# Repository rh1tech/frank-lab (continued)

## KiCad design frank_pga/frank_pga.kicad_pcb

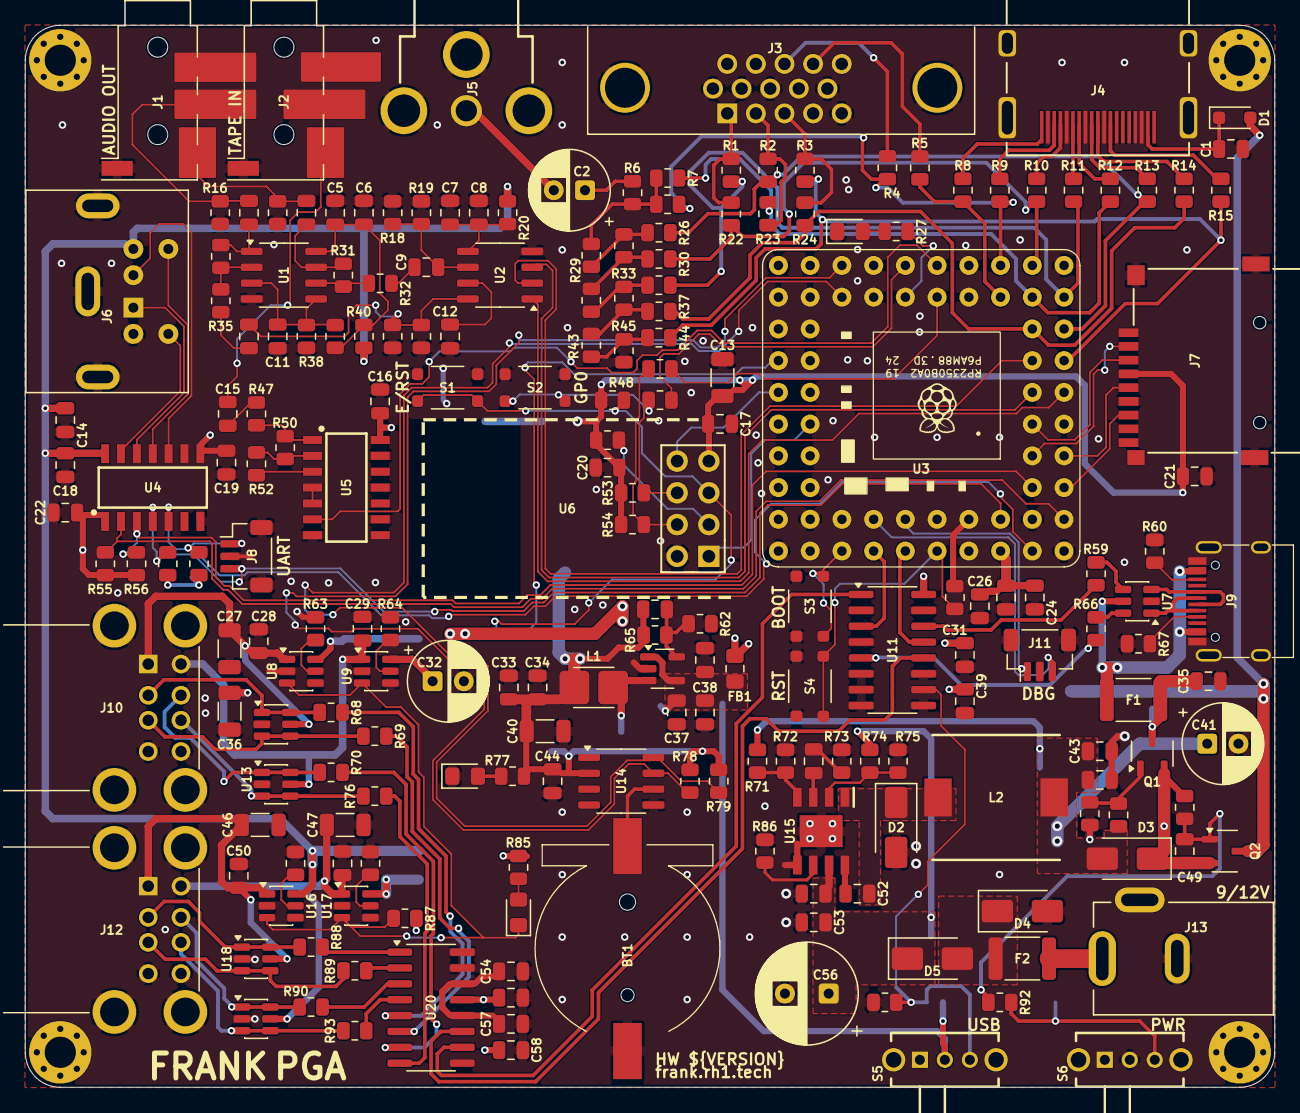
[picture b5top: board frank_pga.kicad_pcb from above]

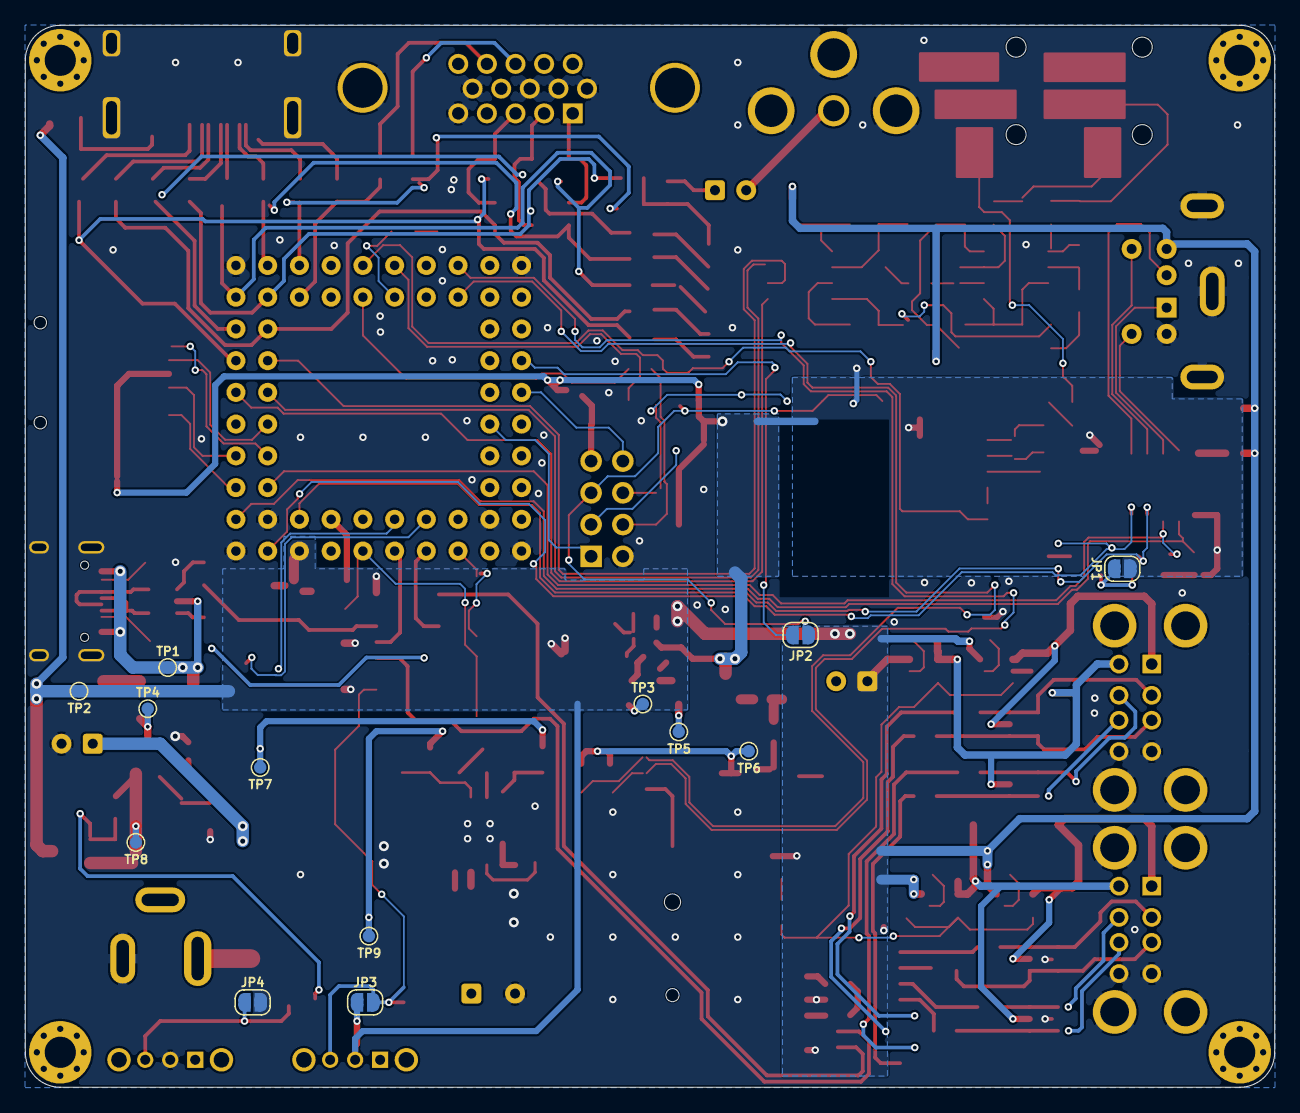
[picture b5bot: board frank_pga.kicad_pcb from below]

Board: 2 copper layers, 100.0 x 85.0 mm, 223 parts (13 on the bottom side), 150 nets.

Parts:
BT1: Battery_CR1220
C1, C5, C7, C14, C15, C16, C17, C18, C19, C21, C22, C24, C26, C28, C29, C37, C39, C44, C48, C50, C51, C52, C54, C55: 100n 50V; C_0805_2012Metric
C2, C32, C41: 220u 10V; C_Radial_D6.3mm_P2.50mm
C3, C4, C6, C8, C9, C10, C11, C12, C20, C23, C30, C31, C33, C34, C35, C38, C43, C45: 10u 16V; C_0805_2012Metric
C13, C27, C36, C40, C46, C47: 100u 10V; C_1206_3216Metric
C25: 22p 50V; C_0805_2012Metric
C42: 150p 50V; C_0805_2012Metric
C49, C57: 1u 16V; C_0805_2012Metric
C53: 10u 25V; C_0805_2012Metric
C56: 680u 25V; C_Radial_D8.0mm_P3.50mm
C58: 4.7u 16V; C_0805_2012Metric
D1: 1N5819WS; D_SOD-323
D2, D3, D5: SS34; D_SMA
D4: SMAJ15A; D_SMA
F1, F2: 1.5A 24V; Fuse_1812_4532Metric
FB1: 600R@100MHz 2A; L_0805_2012Metric
H1, H2, H3, H4: Hole 2.5mm; MountingHole_2.5mm_Pad_Via
J1: PJ-320D; AudioJack_3.5mm_PJ320D_AudioOut
J2: PJ-320D; AudioJack_3.5mm_PJ320D_TapeIn
J3: VGA; DSUB-15_Female
J4: HDMI-001 19PCBTP; HDMI_Female
J5: RCA-103; BarrelJack_RCJ-012
J6: MDC-036; MiniDIN_6pin_Female
J7: 104031-0811; MicroSD_SMD_Long
J8: UART M; JST_SH_1x03_P1.00mm_Vertical
J9: USB4215-03-A; USB_C_Receptacle
J10, J12: SS-52100-004; USB_A_Stacked
J11: DEBUG; JST_SH_1x03_P1.00mm_Vertical
J13: DC 9-12V; BarrelJack_DC-005
JP1: Mouse PU; SolderJumper-2_P1.3mm_Open_RoundedPad1.0x1.5mm
JP2: ESP RST; SolderJumper-2_P1.3mm_Open_RoundedPad1.0x1.5mm
JP3: USB Debug; SolderJumper-2_P1.3mm_Open_RoundedPad1.0x1.5mm
JP4: Force On; SolderJumper-2_P1.3mm_Open_RoundedPad1.0x1.5mm
L1: 2.2u; L_Cenker_CKCS3015_HandSolder
L2: 22u; Inductor_CDRH104RNP
LD1: Blue; LED_0805
LD2: Green; LED_0805
LD3: Red; LED_0805
Q1, Q2: AO3401A; SOT-23-3L_AOS
R1, R2, R3, R46, R49, R77, R81, R85: 1K; R_0805_2012Metric
R4, R5, R20, R27, R40: 100R; R_0805_2012Metric
R6: 51R; R_0805_2012Metric
R7, R8, R9, R10, R11, R12, R13, R14, R15, R26, R30, R34, R37, R44: 270R; R_0805_2012Metric
R16, R17: 20K; R_0805_2012Metric
R18, R42: 470R; R_0805_2012Metric
R19, R32, R35, R38, R39, R41, R48, R51, R53, R54, R55, R56, R57, R58, R61, R91, R92: 10K; R_0805_2012Metric
R21: 750R; R_0805_2012Metric
R22, R23, R24: 330R; R_0805_2012Metric
R25, R29, R33, R36, R43: 150R; R_0805_2012Metric
R28, R31, R71: 47K; R_0805_2012Metric
R45: 300R; R_0805_2012Metric
R47, R78, R79: 4.7K; R_0805_2012Metric
R50, R52, R63, R64, R65, R73, R74, R80, R82, R83, R84, R86, R87: 100K; R_0805_2012Metric
R59, R66, R68, R69, R70, R76, R88, R89, R90, R93: 22R; R_0805_2012Metric
R60, R67: 5.1K; R_0805_2012Metric
R62: 22K; R_0805_2012Metric
R72: 8.2K; R_0805_2012Metric
R75: 30K; R_0805_2012Metric
S1: ESP Reset; Button_SMD_3x4x2mm
S2: ESP Boot; Button_SMD_3x4x2mm
S3: RP Boot; Button_SMD_3x4x2mm
S4: RP Reset; Button_SMD_3x4x2mm
S5: USB MODE; Switch_Slide_SK12D07VG3NS
S6: POWER; Switch_Slide_SK12D07VG3NS
TP1: VBUS_USB; TestPoint_Pad_D1.0mm
TP2: VBUS; TestPoint_Pad_D1.0mm
TP3: +5V_BUCK; TestPoint_Pad_D1.0mm
TP4: VBUS_USB_F; TestPoint_Pad_D1.0mm
TP5: LX; TestPoint_Pad_D1.0mm
TP6: +3V3; TestPoint_Pad_D1.0mm
TP7: +5V_DC; TestPoint_Pad_D1.0mm
TP8: +5V_SEL; TestPoint_Pad_D1.0mm
TP9: VIN_PROT; TestPoint_Pad_D1.0mm
U1: LM358; SO-8
U2: TDA1387T; SO-8
U3: Pimoroni PGA2350; PGA2350
U4: TXS0104EDR; SOIC-14_P1.27mm
U5: CD4069UBM; SOIC-14_P1.27mm
U6: ESP-01 socket; ESP-01S
U7, U12, U13, U18, U19: USBLC6-2SC6; SOT-23-6
U8, U9, U16, U17: CH217K; SOT-23-6
U10: SY8089AAAC; SOT-23-5
U11: 74HC4052D; SOP-16_P1.27mm
U14: DS3231MZ; SO-8
U15: MP1584EN; SOIC-9_P1.27mm
U20: MW7211A; SOP-16_P1.27mm

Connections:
+3V3: C13.1, C16.1, C17.1, C19.1, C20.1, C21.2, C22.1, C25.1, C33.1, C34.1, C40.1, C44.1, J7.4 (VDD), JP1.1 (A), L1.2, R48.1, R51.1, R53.1, R54.1, R55.1, R56.1, R65.1, R77.1, R78.2, R79.2, TP6.1 (1_1), U4.1 (VCCA), U4.8 (OE), U5.14 (VDD), U6.7 (VCC), U14.2 (VCC)
+5V_DC: C41.1, C43.1, C45.2, D3.2 (A), L2.2, R71.1, R81.1, TP7.1 (1_1)
+5V_SEL: C49.1, D3.1 (K), Q1.2 (S), Q2.2 (S), R82.1, TP8.1 (1_1)
/Audio/AMP_OUTL: C4.2, J1.T, R17.2
/Audio/AMP_OUTR: C3.2, J1.R, R16.2
/Audio/TDA_L: C9.1, R18.2, R19.1, U2.6 (A_LEFT)
/Audio/TDA_R: C10.1, R41.1, R42.1, U2.8 (A_RIGHT)
/Composite/CVBS: C2.2, J5.1
/ESP-01/ESP_EN: R51.2, U6.3 (CH_PD)
/ESP-01/ESP_GPIO0: R49.2, R53.2, S2.1, S2.3, U6.6 (GPIO0)
/ESP-01/ESP_GPIO2: R46.2, R54.2, U6.4 (GPIO2)
/ESP-01/ESP_RST: JP2.1 (A), R48.2, S1.1, S1.3, U6.5 (RST)
/HUB2_UP_DM: U11.1 (2Y0), U20.10 (DMU)
/HUB2_UP_DP: U11.12 (1Y0), U20.11 (DPU)
/LED_M_A: LD1.2 (A), R27.2
/M0_PS_MS_CLK: J8.1, R57.2, U3.61 (GP0), U4.4 (A3)
/M1_PS_MS_DAT: J8.3, R58.2, U3.62 (GP1), U4.5 (A4)
/M2_PS_KB_CLK: R55.2, U3.2 (GP2), U4.2 (A1)
/M3_PS_KB_DAT: R56.2, U3.3 (GP3), U4.3 (A2)
/M4_SD_DAT0: J7.7 (DAT0), U3.4 (GP4)
/M5_SD_DAT3: J7.2 (DAT3/CD), U3.5 (GP5)
/M6_SD_CLK: J7.5 (CLK), U3.6 (GP6)
/M7_SD_CMD: J7.3 (CMD), U3.7 (GP7)
/M9_AU_DATA: U2.3 (DATA), U3.9 (GP9)
/M10_AU_SCLK: U2.1 (SCLK), U3.10 (GP10)
/M11_AU_LRCK: U2.2 (LRCK), U3.11 (GP11)
/M12_HV_CLK-_B0: R3.1, R15.2, R44.1, U3.12 (GP12)
/M13_HV_CLK+_B1: R14.2, R24.1, R37.1, U3.13 (GP13)
/M14_HV_D0-_G0: R2.1, R13.2, R26.1, U3.14 (GP14)
/M15_HV_D0+_G1: R7.1, R12.2, R23.1, U3.15 (GP15)
/M16_HV_D1-_R0: R1.1, R11.2, R34.1, U3.16 (GP16)
/M17_HV_D1+_R1: R10.2, R22.1, R30.1, U3.17 (GP17)
/M18_HV_D2-_HS: R4.2, R9.2, R21.1, U3.19 (GP18)
/M19_HV_D2+_VS: R5.2, R8.2, U3.20 (GP19)
/M22_TP_IN: U3.23 (GP22), U5.6 (I=*C)
/M23_ES_GPIO2: R46.1, U3.24 (GP23)
/M24_ES_GPIO0: R49.1, U3.25 (GP24)
/M25_LD: R27.1, U3.26 (GP25)
/M28_RT_SDA: R78.1, U3.29 (GP28), U14.7 (SDA)
/M29_RT_SCL: R79.1, U3.30 (GP29), U14.8 (SCL)
/M36_ES_RST: JP2.2 (B), U3.38 (GP36)
/M38_ES_RX: U3.40 (GP38), U6.8 (URXD)
/M39_ES_TX: U3.41 (GP39), U6.1 (UTXD)
/MCU/BOOTSEL: S3.1, S3.3, U3.51 (BOOTSEL)
/MCU/PGA_3V3: R61.1, U3.59 (3V3)
/MCU/RUN: R61.2, S4.1, S4.3, U3.56 (RUN)
/MCU/SWCLK: J11.3, U3.55 (SWCLK)
/MCU/SWDIO: J11.1, U3.52 (SWDIO)
/M_USB_DM: U3.53 (USB_DM), U11.3 (2Z)
/M_USB_DP: U3.54 (USB_DP), U11.13 (1Z)
/PS2/KB_CLK_5V: J6.5, U4.13 (B1)
/PS2/KB_DATA_5V: J6.1, U4.12 (B2)
/PS2/MS_CLK_5V: J6.6, U4.11 (B3)
/PS2/MS_DATA_5V: J6.2, U4.10 (B4)
/PS_MS_PU: JP1.2 (B), R57.1, R58.1
/Power/+5V_BUCK: C30.1, C37.1, C38.1, FB1.2, TP3.1 (1_1), U10.1 (EN), U10.4 (IN)
/Power/DC_FUSED: D4.1 (K), D5.2 (A), F2.2
/Power/FB: C25.2, R62.1, R65.2, U10.5 (FB)
/Power/VBUS_USB_F: C35.1, F1.2, Q1.3 (D), TP4.1 (1_1)
/Power/VIN_PROT: C51.1, C53.1, C56.1, D5.1 (K), R74.2, TP9.1 (1_1), U15.7 (VIN)
/Tape In/TAPE: C15.2, J2.T
/USB-A/HUB2_VD33: C54.1, C57.1, U20.12 (VD33), U20.14 (VD3)
/USB-A/OC_LED_A: LD3.2 (A), R85.2
/USB-A/P0_DM: R88.1, U20.1 (DM0)
/USB-A/P0_DP: R89.1, U20.2 (DP0)
/USB-A/P1_DM: R90.1, U20.3 (DM1)
/USB-A/P1_DP: R93.1, U20.4 (DP1)
/USB-A/P2_DM: R68.1, U20.5 (DM2)
/USB-A/P2_DP: R69.1, U20.6 (DP2)
/USB-A/P3_DM: R70.1, U20.7 (DM3)
/USB-A/P3_DP: R76.1, U20.8 (DP3)
/USB-A/UA1_DM: J12.2 (D1-), R88.2, U18.1 (I/O1), U18.6 (I/O1)
/USB-A/UA1_DP: J12.3 (D1+), R89.2, U18.3 (I/O2), U18.4 (I/O2)
/USB-A/UA2_DM: J12.6 (D2-), R90.2, U19.1 (I/O1), U19.6 (I/O1)
/USB-A/UA2_DP: J12.7 (D2+), R93.2, U19.3 (I/O2), U19.4 (I/O2)
/USB-A/UA3_DM: J10.2 (D1-), R68.2, U12.1 (I/O1), U12.6 (I/O1)
/USB-A/UA3_DP: J10.3 (D1+), R69.2, U12.3 (I/O2), U12.4 (I/O2)
/USB-A/UA4_DM: J10.6 (D2-), R70.2, U13.1 (I/O1), U13.6 (I/O1)
/USB-A/UA4_DP: J10.7 (D2+), R76.2, U13.3 (I/O2), U13.4 (I/O2)
/USB-A/UA_ISET1: R83.1, U16.5 (ISET)
/USB-A/UA_ISET2: R84.1, U17.5 (ISET)
/USB-A/UA_ISET3: R63.1, U8.5 (ISET)
/USB-A/UA_ISET4: R64.1, U9.5 (ISET)
/USB-A/USB_OC: LD3.1 (K), R87.2, U8.3 (FLAG#), U9.3 (FLAG#), U16.3 (FLAG#), U17.3 (FLAG#)
/USB-A/VBUS_A1: C46.1, C50.1, J12.1 (VBUS1), U16.1 (VOUT), U18.5 (VBUS)
/USB-A/VBUS_A2: C47.1, C48.1, J12.5 (VBUS2), U17.1 (VOUT), U19.5 (VBUS)
/USB-A/VBUS_A3: C27.1, C28.1, J10.1 (VBUS1), U8.1 (VOUT), U12.5 (VBUS)
/USB-A/VBUS_A4: C29.1, C36.1, J10.5 (VBUS2), U9.1 (VOUT), U13.5 (VBUS)
/USB/UC_CC1: J9.4 (CC1), R67.1
/USB/UC_CC2: J9.10 (CC2), R60.1
/USB/UC_DM: R66.1, U11.5 (2Y1)
/USB/UC_DM_C: J9.5 (DN2), J9.7 (DN1), U7.1 (I/O1)
/USB/UC_DM_E: R66.2, U7.6 (I/O1)
/USB/UC_DP: R59.1, U11.14 (1Y1)
/USB/UC_DP_C: J9.6 (DP1), J9.8 (DP2), U7.3 (I/O2)
/USB/UC_DP_E: R59.2, U7.4 (I/O2)
/USB/USB_MODE: JP3.2 (B), R91.1, S5.3, U11.10 (S0)
/VBUS_USB: F1.1, J9.2 (VBUS), J9.11 (VBUS), TP1.1 (1_1), U7.5 (VBUS)
GND: BT1.2 (-), C1.2, C5.1, C6.2, C7.2, C8.2, C11.1, C12.2, C13.2, C14.2, C16.2, C17.2, C18.2, C19.2, C20.2, C21.1, C22.2, C23.2, C24.2, C26.2, C27.2, C28.2, C29.2, C30.2, C31.2, C32.2, C33.2, C34.2, C35.2, C36.2, C37.2, C38.2, C39.2, C40.2, C41.2, C43.2, C44.2, C45.1, C46.2, C47.2, C48.2, C50.2, C51.2, C53.2, C54.2, C55.2, C56.2, C57.2, C58.2, D2.2 (A), D4.2 (A), J1.S, J2.S, J3.0, J3.5, J3.6, J3.7, J3.8, J3.10, J4.2 (G_D2), J4.5 (G_D1), J4.8 (G_D0), J4.11 (G_CLK), J4.17 (G_DDC/CEC), J4.20 (SHIELD1), J4.21 (SHIELD2), J4.22 (SHIELD3), J4.23 (SHIELD4), J5.2, J6.3, J7.6 (VSS), J7.SH (SHIELD), J8.2, J9.1 (GND), J9.12 (GND), J9.13 (SHIELD), J10.4 (GND1), J10.8 (GND2), J10.9 (Shield), J11.2, J12.4 (GND1), J12.8 (GND2), J12.9 (Shield), J13.2, JP4.1 (A), LD1.1 (K), LD2.1 (K), R16.1, R17.1, R18.1, R19.2, R38.1, R41.2, R42.2, R45.1, R60.2, R62.2, R63.2, R64.2, R67.2, R72.1, R73.2, R75.2, R80.2, R83.2, R84.2, R86.2, R91.2, S1.2, S1.4, S2.2, S2.4, S3.2, S3.4, S4.2, S4.4, S6.2, U1.4 (V-), U2.4 (AGND), U3.1 (GND), U3.18 (GND), U3.33 (GND), U3.48 (GND), U4.7 (GND), U5.7 (VSS), U5.9 (D14), U5.11 (E), U5.13 (F), U6.2 (GND), U7.2 (GND), U8.2 (GND), U8.4 (EN#), U9.2 (GND), U9.4 (EN#), U10.2 (GND), U11.2 (2Y2), U11.4 (2Y3), U11.6 (~E), U11.7 (VEE), U11.8 (GND), U11.9 (S1), U11.11 (1Y3), U11.15 (1Y2), U12.2 (GND), U13.2 (GND), U14.5 (GND), U15.5 (GND), U15.9 (EP), U16.2 (GND), U16.4 (EN#), U17.2 (GND), U17.4 (EN#), U18.2 (GND), U19.2 (GND), U20.15 (GND), U20.16 (GND)
unnamed: BT1.1 (+), U14.6 (VBAT)
unnamed: C2.1, R6.2
unnamed: C3.1, R28.1, U1.1
unnamed: C4.1, R31.1, U1.7
unnamed: C9.2, R32.2
unnamed: C10.2, R35.2
unnamed: C15.1, R47.2
unnamed: C42.2, R73.1
unnamed: C1.1, D1.1 (K), J4.18 (+5V)
unnamed: C52.2, D2.1 (K), L2.1, U15.1 (SW)
unnamed: F2.1, J13.1
unnamed: J3.1, R1.2, R22.2
unnamed: J3.2, R2.2, R23.2
unnamed: J3.3, R3.2, R24.2
unnamed: J3.13, R4.1
unnamed: J3.14, R5.1
unnamed: J4.12 (CLKN), R15.1
unnamed: J4.10 (CLKP), R14.1
unnamed: J4.9 (D0N), R13.1
unnamed: J4.7 (D0P), R12.1
unnamed: J4.6 (D1N), R11.1
unnamed: J4.4 (D1P), R10.1
unnamed: J4.3 (D2N), R9.1
unnamed: J4.1 (D2P), R8.1
unnamed: JP4.2 (B), R92.2, S6.3
unnamed: LD2.2 (A), R77.2
unnamed: Q1.1 (G), R80.1, R81.2
unnamed: C49.2, Q2.1 (G), R82.2, R92.1
unnamed: R6.1, R7.2, R21.2, R29.2
unnamed: R25.1, R30.2, R36.2
unnamed: R25.2, R26.2, R29.1
unnamed: R33.1, R37.2, R43.2
unnamed: R33.2, R34.2, R36.1
unnamed: R43.1, R44.2, R45.2
unnamed: C11.2, R38.2, R39.1, U1.3 (+), U1.5 (+)
unnamed: R28.2, R35.1, U1.2 (-)
unnamed: R31.2, R32.1, U1.6 (-)
unnamed: C5.2, C6.1, R39.2, R40.2, U1.8 (V+)
unnamed: C12.1, U2.7 (FLT)
unnamed: C7.1, C8.1, R20.1, U2.5 (VA)
unnamed: R47.1, R50.2, U5.1 (A)
unnamed: R52.1, U5.3 (B)
unnamed: U5.4 (H=*B), U5.5 (C)
unnamed: R50.1, R52.2, U5.2 (G-*A)
unnamed: L1.1, TP5.1 (1_1), U10.3 (LX)
unnamed: C52.1, U15.8 (BST)
unnamed: C42.1, U15.3 (COMP)
unnamed: R74.1, R75.1, U15.2 (EN)
unnamed: R71.2, R72.2, U15.4 (FB)
unnamed: R86.1, U15.6 (FREQ)
VBUS: C14.1, C18.1, C23.1, C24.1, C26.1, C31.1, C32.1, C39.1, C55.1, C58.1, D1.2 (A), FB1.1, J6.4, JP3.1 (A), Q2.3 (D), R20.2, R40.1, R85.1, R87.1, S5.2, TP2.1 (1_1), U3.60 (VBUS), U4.14 (VCCB), U8.6 (VIN), U9.6 (VIN), U11.16 (VCC), U16.6 (VIN), U17.6 (VIN), U20.13 (VDD5)

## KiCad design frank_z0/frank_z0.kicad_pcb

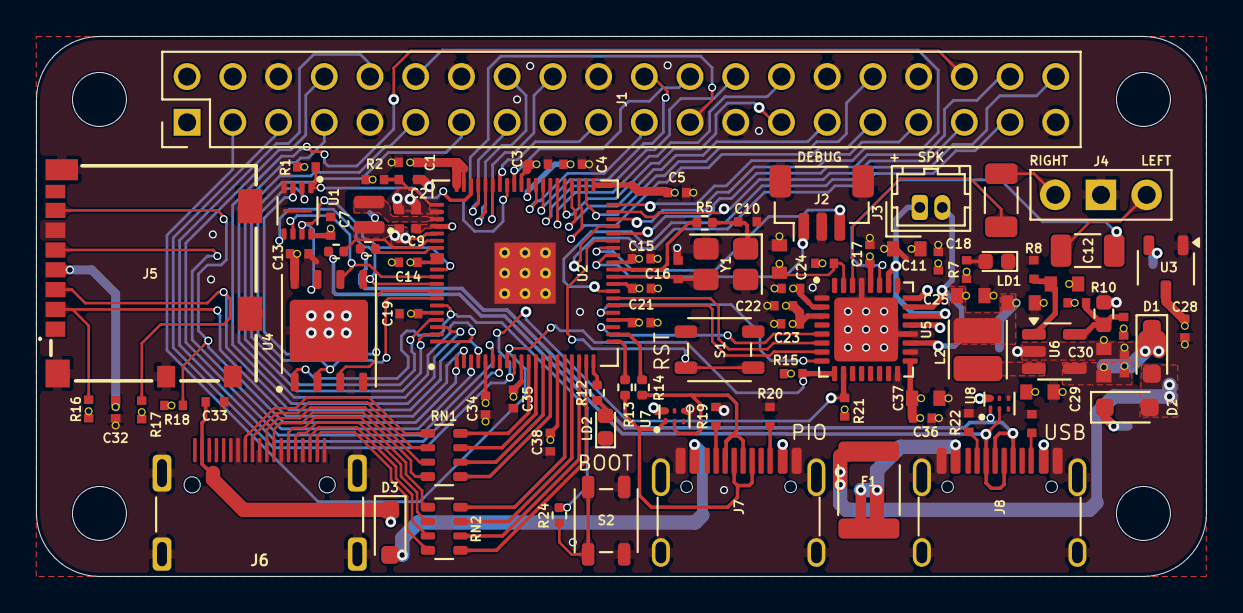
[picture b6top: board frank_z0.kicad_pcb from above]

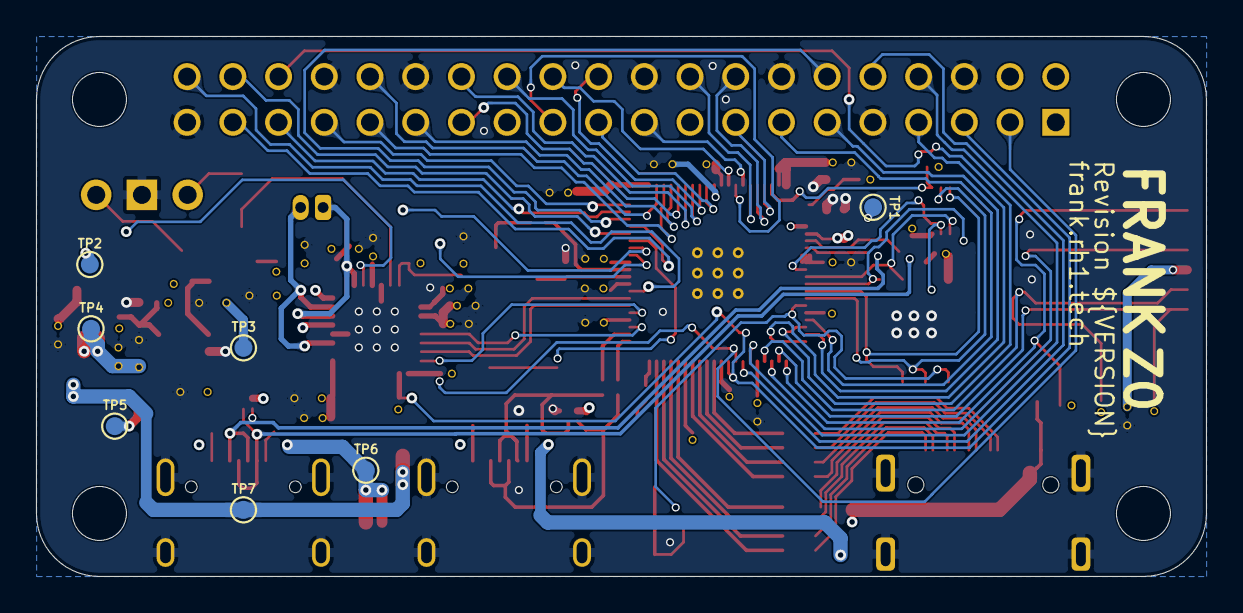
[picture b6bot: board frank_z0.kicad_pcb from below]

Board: 4 copper layers, 65.0 x 30.0 mm, 103 parts (7 on the bottom side), 101 nets.

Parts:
C1, C4, C5, C14, C17, C18, C20, C21, C22, C24, C31, C32, C34, C36: 100n 16V; C_0402_1005Metric_small_pads_Via_GND
C2, C8, C9: 4.7u 10V; C_0402_1005Metric_small_pads
C3, C7, C13, C19, C35, C38: 100n 16V; C_0402_1005Metric_small_pads_Via
C6, C12: 100u 10V; C_1206_3216Metric
C10, C16: 15p 50V; C_0402_1005Metric_small_pads
C11, C25, C26, C29, C30, C37: 10u 25V; C_0603_1608Metric_small_pads_Via_GND
C15: 4.7u 10V; C_0402_1005Metric_small_pads_Via_GND
C23, C28: 1u 25V; C_0402_1005Metric_small_pads_Via_GND
C27: 22p 50V; C_0402_1005Metric_small_pads_Via
C33: 100n 16V; C_0402_1005Metric_small_pads
C39: 1u 50V; C_0603_1608Metric_small_pads_Via_GND
D1, D2, D3: 1N5819WS; D_SOD-323
F1: 1.5A 6V; Fuse_1812_4532Metric
H1, H2, H3, H4: Mounting Hole (3.0mm); MountingHole_3.0mm
J1: GPIO; PinHeader_2x20_P2.54mm_Vertical
J2: Debug; JST_SH_1x03_P1.00mm_Vertical
J3: Speaker; JST_GH_1x02_P1.25mm
J4: Headphones; PinHeader_1x03_P2.54mm_Vertical
J5: 104031-0811
J6: XDHF-1903-1064; HDMI_Mini_Female
J7, J8: KH-TYPE-C-16P; USB_C_Receptacle
L1: 3.3µH; L_AOTA-B201610_2.0x1.6mm
L2: 2.2u; L_Cenker_CKCS3015
LD1: Green; LED_0603_1608Metric
LD2: Blue; LED_0603_1608Metric
R1, R6, R16, R17, R18: 10K; R_0402_1005Metric_small_pads_Via
R2: 33R; R_0402_1005Metric_small_pads_Via
R3, R4: 27R; R_0402_1005Metric
R5, R24: 1K; R_0402_1005Metric
R7: 1K; R_0402_1005Metric_small_pads_Via
R8: 100K 1%; R_0402_1005Metric_small_pads
R9: 150K 1%; R_0603_1608Metric_small_pads_Via
R10: 22K 1%; R_0603_1608Metric
R11: 100K 1%; R_0402_1005Metric_small_pads_Via
R12: 100R; R_0402_1005Metric
R13, R14: 22R; R_0402_1005Metric
R15, R21: 4.7K; R_0402_1005Metric_small_pads_Via
R19, R20, R22, R23: 5.1K; R_0402_1005Metric_small_pads
RN1, RN2: 270R; R_Array_4x0603
S1: RP Reset; Button_TS-1233_3.3x3.3mm
S2: RP Boot; Button_TS-1233_3.3x3.3mm
TP1: +1V1_A; TestPoint_Pad_D1.0mm
TP2: +1V8; TestPoint_Pad_D1.0mm
TP3: +3V3; TestPoint_Pad_D1.0mm
TP4: VBUS; TestPoint_Pad_D1.0mm
TP5: M_HV_5V; TestPoint_Pad_D1.0mm
TP6: VBUS_USB; TestPoint_Pad_D1.0mm
TP7: VBUS_USB_F; TestPoint_Pad_D1.0mm
U1: APS6404L-3SQR-ZR; PSON50P200X300X50-9N
U2: RP2350B; RP2350-QFN-80_10x10_P0.4mm
U3: XC6206P182MR; XC6206P182MR-G
U4: W25Q128JVPIQ; WSON-8-1EP_6x5mm_P1.27mm_EP3.45x4.35mm
U5: TLV320DAC3100IRHBR
U6: SY8089AAAC; SOT-23-5
U7, U8: TPD4S012DRYR
Y1: 12 MHz; Crystal_SMD_3225-4Pin_3.2x2.5mm

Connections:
+1V1_A: C3.1, C8.1, C15.1, C35.1, L1.1, TP1.1 (1_1), U2.10 (DVDD), U2.32 (DVDD), U2.51 (DVDD), U2.65 (VREG_FB)
+1V8: C22.1, C23.1, TP2.1 (1_1), U3.2 (VOUT), U5.3 (DVDD)
+3V3: C1.1, C4.1, C5.1, C7.1, C9.1, C13.1, C14.1, C17.1, C19.1, C20.1, C21.1, C24.1, C25.1, C26.1, C27.1, C28.1, C29.1, C32.1, C34.1, C36.1, C37.1, C38.1, J1.1, J1.17, J5.4 (VDD), L2.2, R1.1, R2.1, R6.1, R7.1, R11.1, R15.1, R16.1, R17.1, R18.1, R21.1, TP3.1 (1_1), U1.8 (VDD), U2.5 (IOVDD), U2.15 (IOVDD), U2.24 (IOVDD), U2.29 (IOVDD), U2.41 (IOVDD), U2.50 (IOVDD), U2.59 (ADC_AVDD), U2.60 (IOVDD), U2.64 (VREG_VIN), U2.68 (USB_OTP_VDD), U2.69 (QSPI_IOVDD), U2.76 (IOVDD), U3.3 (VIN), U4.8 (VCC), U5.2 (IOVDD), U5.17 (AVDD), U5.28 (HPVDD)
/Audio/SPKM: J3.2, U5.19 (SPKM_1), U5.23 (SPKM_2)
/Audio/SPKP: J3.1, U5.22 (SPKP_1), U5.26 (SPKP_2)
/M0_HD_P13: J1.13, U2.77 (GPIO0)
/M1_HD_P36: J1.36, U2.78 (GPIO1)
/M2_HD_P11: J1.11, U2.79 (GPIO2)
/M3_HD_P7: J1.7, U2.80 (GPIO3)
/M4_SD_DAT0: J5.7 (DAT0), R18.2, U2.1 (GPIO4)
/M5_SD_DAT3: J5.2 (DAT3/CD), R16.2, U2.2 (GPIO5)
/M6_SD_CLK: J5.5 (CLK), U2.3 (GPIO6)
/M7_SD_CMD: J5.3 (CMD), R17.2, U2.4 (GPIO7)
/M8_HD_TX: J1.8, U2.6 (GPIO8)
/M9_HD_RX: J1.10, U2.7 (GPIO9)
/M10_AU_SDA: J1.3, R15.2, U2.8 (GPIO10), U5.9 (SDA)
/M11_AU_SCL: J1.5, R21.2, U2.9 (GPIO11), U5.10 (SCL)
/M12_HV_CLKN: RN1.4 (R4.1), U2.11 (GPIO12)
/M13_HV_CLKP: RN1.3 (R3.1), U2.12 (GPIO13)
/M14_HV_D0N: RN1.2 (R2.1), U2.13 (GPIO14)
/M15_HV_D0P: RN1.1 (R1.1), U2.14 (GPIO15)
/M16_HV_D1N: RN2.4 (R4.1), U2.16 (GPIO16)
/M17_HV_D1P: RN2.3 (R3.1), U2.17 (GPIO17)
/M18_HV_D2N: RN2.2 (R2.1), U2.18 (GPIO18)
/M19_HV_D2P: RN2.1 (R1.1), U2.19 (GPIO19)
/M21_PU_DP: R13.2, U2.21 (GPIO21)
/M22_PU_DM: R14.2, U2.22 (GPIO22)
/M23_AU_DIN: U2.23 (GPIO23), U5.5 (DIN)
/M24_AU_MCLK: U2.25 (GPIO24), U5.8 (MCLK)
/M25_AU_BCLK: U2.26 (GPIO25), U5.7 (BCLK)
/M26_AU_WCLK: U2.27 (GPIO26), U5.6 (WCLK)
/M27_HD_P40: J1.40, U2.28 (GPIO27)
/M28_HD_P38: J1.38, U2.36 (GPIO28)
/M29_HD_P37: J1.37, U2.37 (GPIO29)
/M30_HD_P12: J1.12, U2.38 (GPIO30)
/M31_HD_P35: J1.35, U2.39 (GPIO31)
/M32_HD_P33: J1.33, U2.40 (GPIO32)
/M33_HD_P32: J1.32, U2.42 (GPIO33)
/M34_HD_P31: J1.31, U2.43 (GPIO34)
/M35_HD_P29: J1.29, U2.44 (GPIO35)
/M36_HD_P27: J1.27, U2.45 (GPIO36)
/M37_HD_P28: J1.28, U2.46 (GPIO37)
/M38_HD_P26: J1.26, U2.47 (GPIO38)
/M39_HD_P22: J1.22, U2.48 (GPIO39)
/M40_HD_P21: J1.21, U2.49 (GPIO40_ADC0)
/M41_HD_P24: J1.24, U2.52 (GPIO41_ADC1)
/M42_HD_P23: J1.23, U2.53 (GPIO42_ADC2)
/M43_HD_P19: J1.19, U2.54 (GPIO43_ADC3)
/M44_HD_P18: J1.18, U2.55 (GPIO44_ADC4)
/M45_HD_P16: J1.16, U2.56 (GPIO45_ADC5)
/M46_HD_P15: J1.15, U2.57 (GPIO46_ADC6)
/M_AU_HPL: C12.1, J4.1
/M_AU_HPR: C6.1, J4.3
/M_USB_DM: J8.5 (DN2), J8.7 (DN1), R3.1, U8.2 (D-_)
/M_USB_DP: J8.6 (DP1), J8.8 (DP2), R4.1, U8.1 (D+)
/Power/FB: C27.2, R10.1, R11.2, U6.5 (FB)
/Power/VBUS_USB_F: D1.2 (A), D2.2 (A), F1.2, TP7.1 (1_1)
/RP2350B/BOOT: R24.2, S2.1, S2.2
/RP2350B/M20_LD_LED: R12.2, U2.20 (GPIO20)
/RP2350B/M47_PR_CS: R1.2, U1.1 (~CE), U2.58 (GPIO47_ADC7)
/RP2350B/QSPI_SCLK: U1.6 (SCLK), U2.71 (QSPI_SCLK), U4.6 (CLK)
/RP2350B/QSPI_SD0: U1.5 (SI/SIO(0)), U2.72 (QSPI_SD0), U4.5 (DI_(IO0))
/RP2350B/QSPI_SD1: U1.2 (SO/SIO(1)), U2.74 (QSPI_SD1), U4.2 (DO_(IO1))
/RP2350B/QSPI_SD2: U1.3 (SIO(2)), U2.73 (QSPI_SD2), U4.3 (~WP_(IO2))
/RP2350B/QSPI_SD3: U1.7 (SIO(3)), U2.70 (QSPI_SD3), U4.7 (~HOLD_OR_/RESET_(IO3))
/RP2350B/QSPI_SS: R24.1, U2.75 (QSPI_SS), U4.1 (~CS)
/RP2350B/RUN: S1.1, S1.2, U2.35 (RUN)
/RP2350B/SWCLK: J2.3, U2.33 (SWCLK)
/RP2350B/SWD: J2.1, U2.34 (SWD)
/RP2350B/VREG_AVDD: C2.1, R2.2, U2.61 (VREG_AVDD)
/RP2350B/VREG_LX: L1.2, U2.63 (VREG_LX)
/RP2350B/XIN: C16.1, U2.30 (XIN), Y1.3
/RP2350B/XOUT: R5.2, U2.31 (XOUT)
/VBUS_USB: F1.1, J8.2 (VBUS), J8.11 (VBUS), TP6.1 (1_1), U8.6 (VBUS)
GND: C1.2, C2.2, C3.2, C4.2, C5.2, C7.2, C8.2, C9.2, C10.2, C11.2, C13.2, C14.2, C15.2, C16.2, C17.2, C18.2, C19.2, C20.2, C21.2, C22.2, C23.2, C24.2, C25.2, C26.2, C28.2, C29.2, C30.2, C31.2, C32.2, C33.2, C34.2, C35.2, C36.2, C37.2, C38.2, C39.2, J1.6, J1.9, J1.14, J1.20, J1.25, J1.30, J1.34, J1.39, J2.2, J4.2, J5.6 (VSS), J5.SH (SHIELD), J6.1 (G_D2), J6.4 (G_D1), J6.7 (G_D0), J6.10 (G_CLK), J6.13 (G_DDC/CEC), J6.SH (SHIELD4), J7.1 (GND), J7.12 (GND), J7.13 (SHIELD), J8.1 (GND), J8.12 (GND), J8.13 (SHIELD), LD1.1 (K), LD2.1 (K), R8.2, R10.2, R19.1, R20.2, R22.1, R23.2, S1.3, S1.4, S2.3, S2.4, U1.4 (VSS), U1.9 (EXP), U2.62 (VREG_PGND), U2.81 (GND), U3.1 (VSS), U4.4 (GND_1), U4.9 (GND_2), U5.1 (IOVSS), U5.16 (AVSS), U5.18 (DVSS), U5.20 (SPKVSS_1), U5.25 (SPKVSS_2), U5.29 (HPVSS), U5.33 (EP), U6.2 (GND), U7.4 (GND), U8.4 (GND), Y1.2, Y1.4
M_HV_5V: C33.1, D2.1 (K), D3.1 (K), J6.18 (+5V), TP5.1 (1_1)
unnamed: C10.1, R5.1, Y1.1
unnamed: J6.12 (CLKN), RN1.5 (R4.2)
unnamed: J6.11 (CLKP), RN1.6 (R3.2)
unnamed: J6.9 (D0N), RN1.7 (R2.2)
unnamed: J6.8 (D0P), RN1.8 (R1.2)
unnamed: J6.6 (D1N), RN2.5 (R4.2)
unnamed: J6.5 (D1P), RN2.6 (R3.2)
unnamed: J6.3 (D2N), RN2.7 (R2.2)
unnamed: J6.2 (D2P), RN2.8 (R1.2)
unnamed: J7.4 (CC1), R19.2
unnamed: J7.10 (CC2), R20.1
unnamed: J7.5 (DN2), J7.7 (DN1), R14.1, U7.2 (D-_)
unnamed: J7.6 (DP1), J7.8 (DP2), R13.1, U7.1 (D+)
unnamed: J8.4 (CC1), R22.2
unnamed: J8.10 (CC2), R23.1
unnamed: LD1.2 (A), R7.2
unnamed: LD2.2 (A), R12.1
unnamed: R3.2, U2.66 (USB_DM)
unnamed: R4.2, U2.67 (USB_DP)
unnamed: C12.2, U5.27 (HPL)
unnamed: C6.2, U5.30 (HPR)
unnamed: C39.1, R6.2, U5.31 (~RESET)
unnamed: R8.1, R9.2, U6.1 (EN)
unnamed: L2.1, U6.3 (LX)
VBUS: C11.1, C18.1, C30.1, C31.1, D1.1 (K), D3.2 (A), J1.2, J1.4, J7.2 (VBUS), J7.11 (VBUS), R9.1, TP4.1 (1_1), U5.21 (SPKVDD_1), U5.24 (SPKVDD_2), U6.4 (IN), U7.6 (VBUS)

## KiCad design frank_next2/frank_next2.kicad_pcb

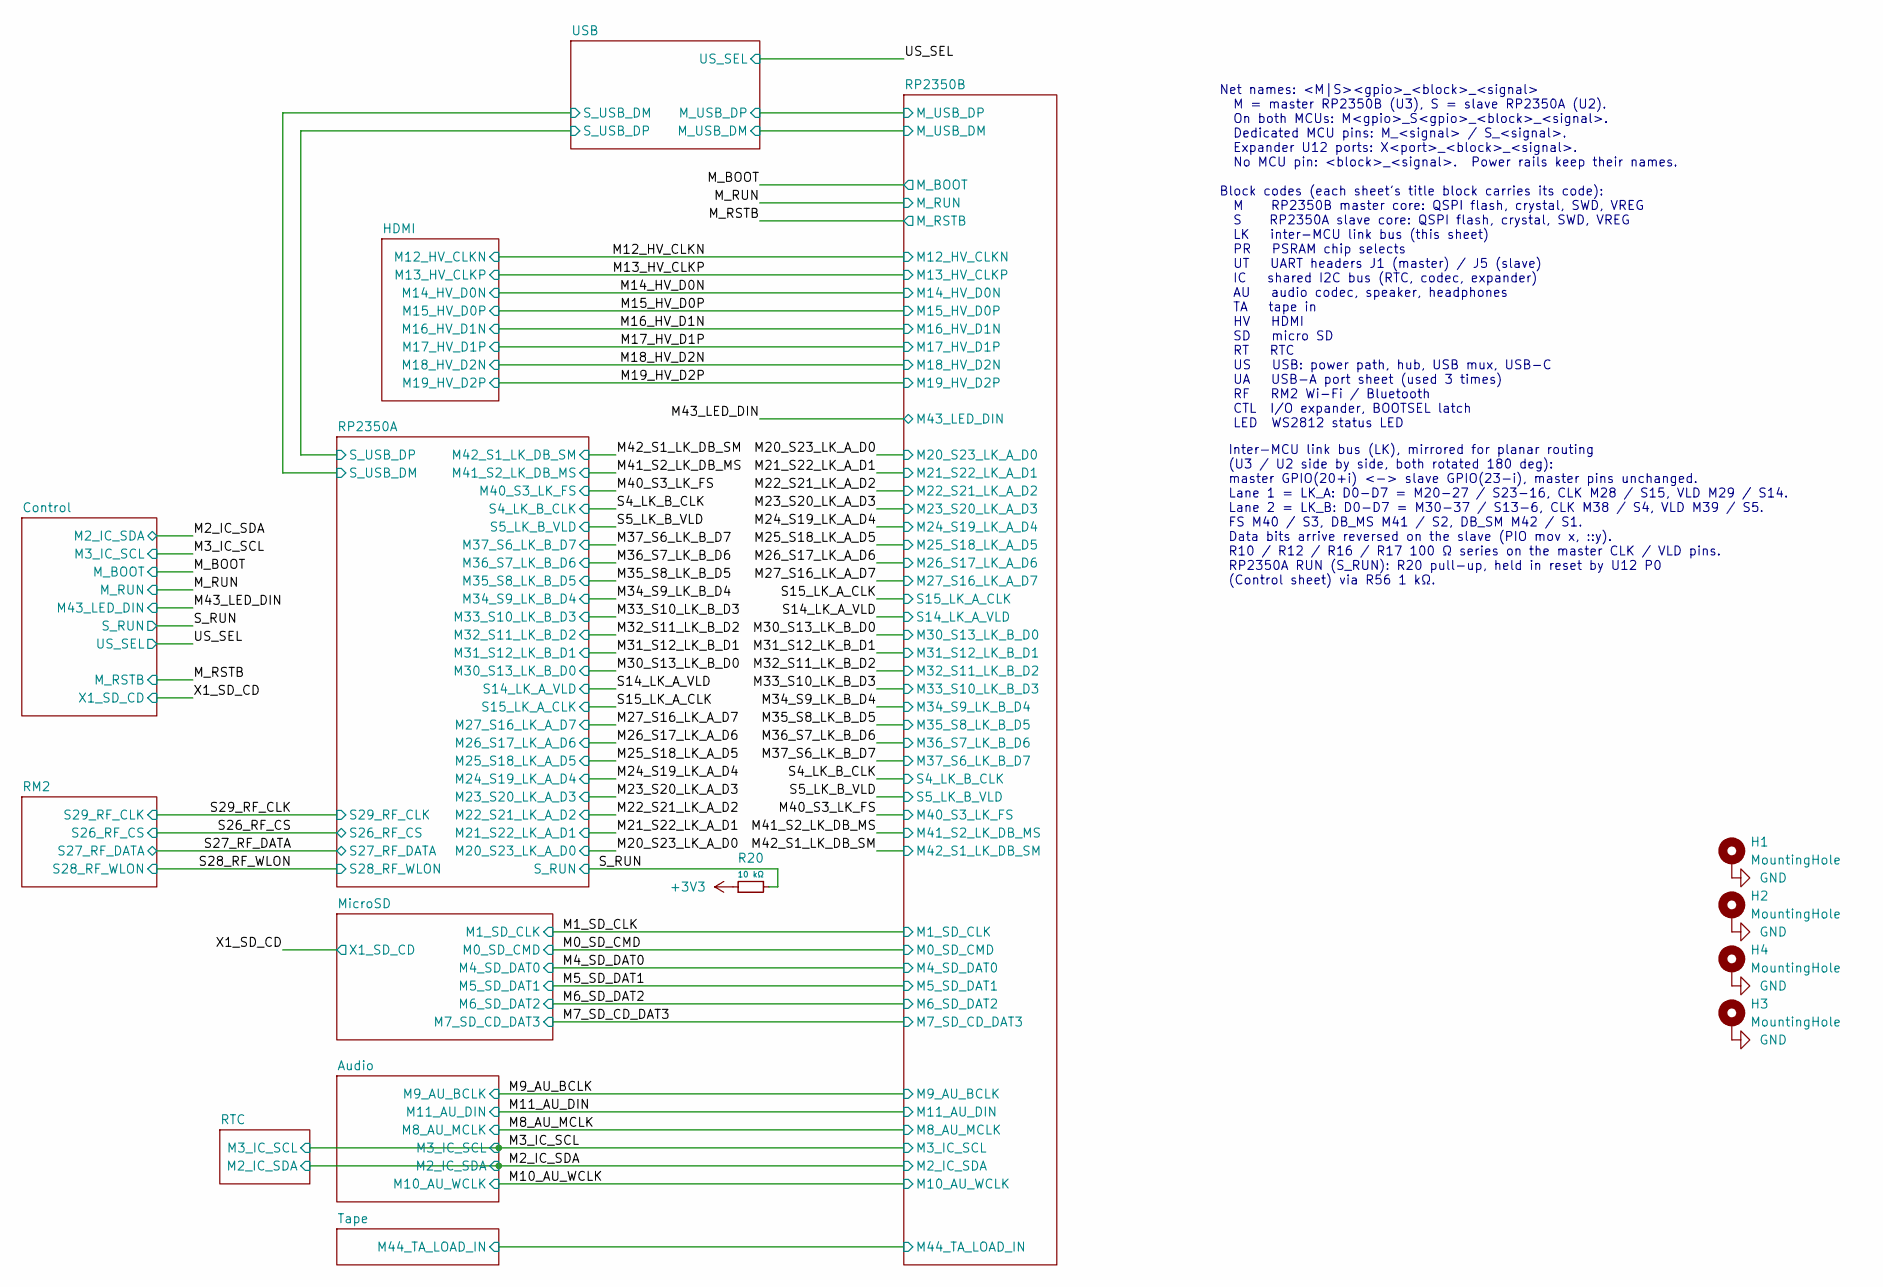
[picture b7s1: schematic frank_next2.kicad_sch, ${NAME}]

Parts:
H1, H2, H3, H4: MountingHole; MountingHole_2.5mm_Pad_Via
R20: 10 kΩ; R_0603_1608Metric_small_pads_Via; LCSC C2906982

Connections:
+3V3: R20.1; also elsewhere on the board
/S_RUN: R20.2; also elsewhere on the board
GND: H1.1 (1_1), H2.1 (1_1), H3.1 (1_1), H4.1 (1_1); also elsewhere on the board

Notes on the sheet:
Net names: <M|S><gpio>_<block>_<signal> M = master RP2350B (U3), S = slave RP2350A (U2). On both MCUs: M<gpio>_S<gpio>_<block>_<signal>. Dedicated MCU pins: M_<signal> / S_<signal>. Expander U12 ports: X<port>_<block>_<signal>. No MCU pin: <block>_<signal>. Power rails keep their names. Block codes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
Inter-MCU link bus (LK), mirrored for planar routing (U3 / U2 side by side, both rotated 180 deg): master GPIO(20+i) <-> slave GPIO(23-i), master pins unchanged. Lane 1 = LK_A: D0-D7 = M20-27 / S23-16, CLK M28 / S15, VLD M29 / S14. Lane 2 = LK_B: D0-D7 = M30-37 / S13-6, CLK M38 / S4, VLD M39 / S5. 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
